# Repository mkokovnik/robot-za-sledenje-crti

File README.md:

# robot-za-sledenje-crti
mehatronski sistemi

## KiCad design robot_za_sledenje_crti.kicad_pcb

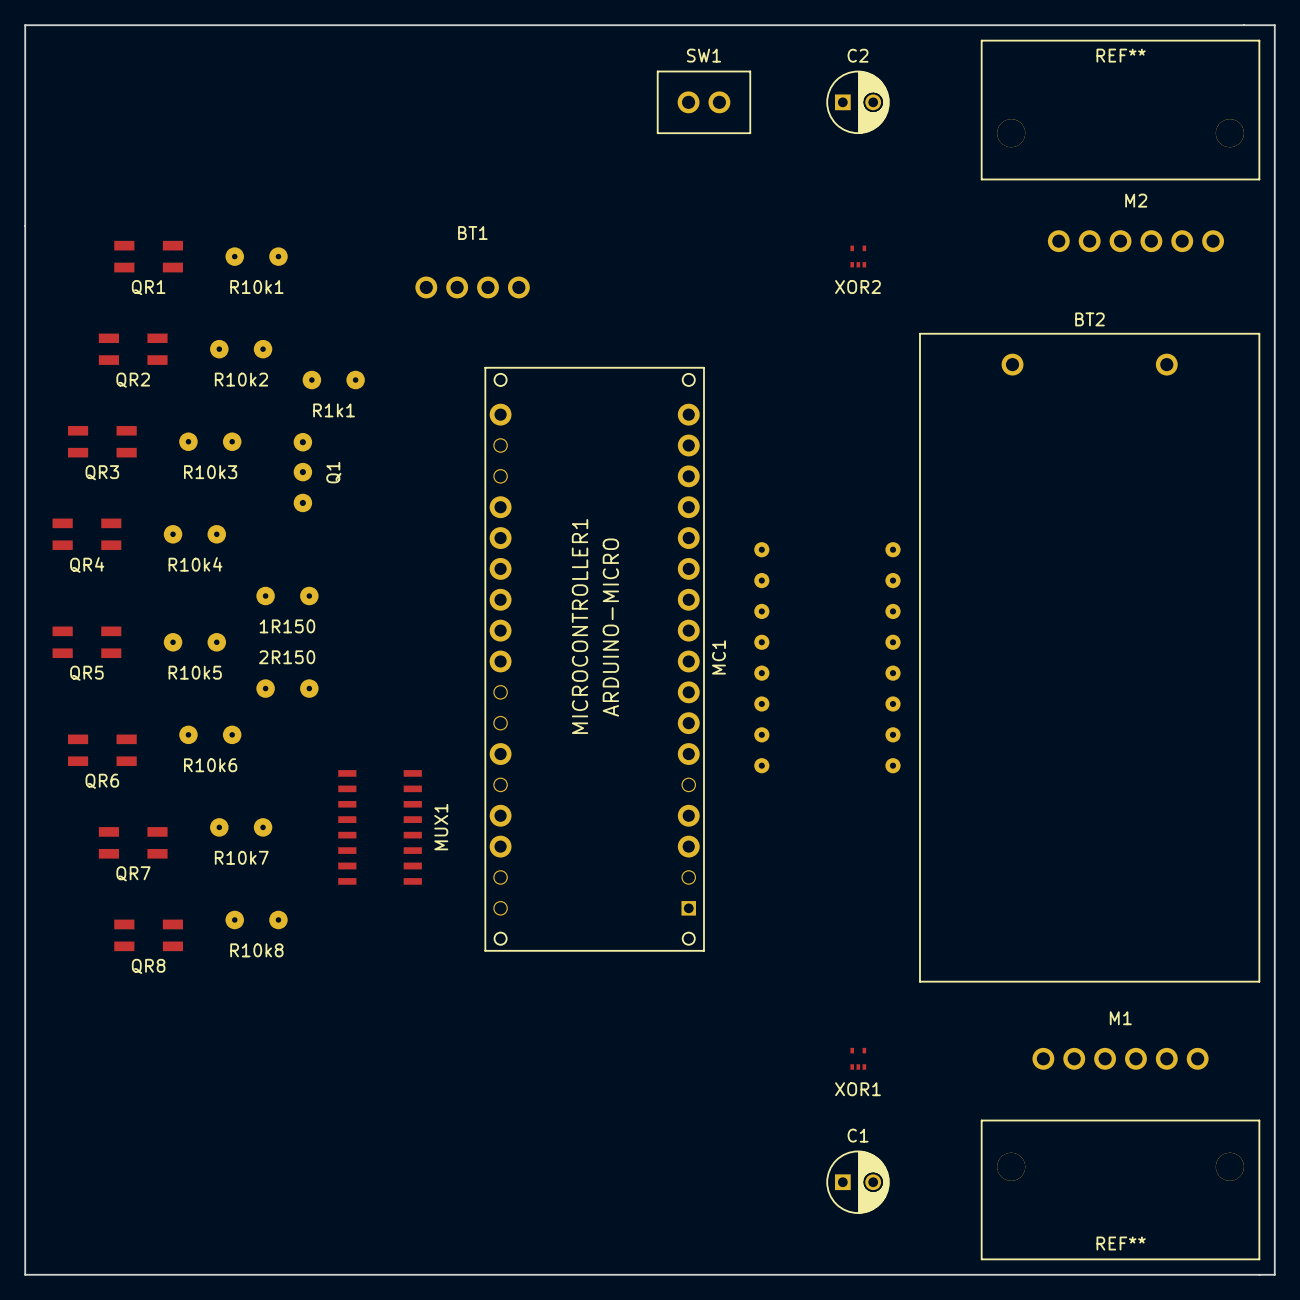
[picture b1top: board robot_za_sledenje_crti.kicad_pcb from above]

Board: 2 copper layers, 102.9 x 102.9 mm, 32 parts (0 on the bottom side), 37 nets, no tracks yet.

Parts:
1R150, 2R150: R; R150
BT1: JY-MCU; JY_MCU
BT2: Battery_Cell; Baterry
C1: CMD; C_Radial_D5_L6_P2.5
C2: CML; C_Radial_D5_L6_P2.5
M1, M2: Motor_Encoder; EM_Encoder
MC1: L293_MOTOR_CONTROLLER
MICROCONTROLLER1: ARDUINO-MICRO; ARDUINO_MICRO_SHIELD
MUX1: 4051; mux4051
Q1: Q_NPN_BCE; npn-10v
QR1, QR2, QR3, QR4, QR5, QR6, QR7, QR8: QRE1113
R1k1: R; R1k
R10k1, R10k2, R10k3, R10k4, R10k5, R10k6, R10k7, R10k8: R; R10k
SW1: SWITCH; switch
XOR1, XOR2: XOR-Gate; XOR-GATE

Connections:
+5V: BT1.4, M1.3, M2.3, MC1.1, MC1.9, MC1.16, R10k1.1, R10k2.1, R10k3.1, R10k4.1, R10k5.1, R10k6.1, R10k7.1, R10k8.1, XOR1.5, XOR2.5
ENCDA: M1.4, MICROCONTROLLER1.8, XOR1.1
ENCLA: M2.4, MICROCONTROLLER1.7, XOR2.1
GND: BT1.3, M1.6, M2.6, MC1.4, MC1.5, MC1.12, MC1.13, MUX1.6, MUX1.7, Q1.3, QR1.4, QR2.4, QR3.4, QR4.4, QR5.4, QR6.4, QR7.4, QR8.4, SW1.2, XOR1.3, XOR2.3
unnamed: 1R150.2, QR1.1
unnamed: 2R150.2, QR5.1
unnamed: BT1.1, MICROCONTROLLER1.3
unnamed: BT1.2, MICROCONTROLLER1.4
unnamed: BT2.2, SW1.1
unnamed: C1.1, M1.1, MC1.3
unnamed: C1.2, M1.2, MC1.6
unnamed: C2.1, M2.1, MC1.11
unnamed: C2.2, M2.2, MC1.14
unnamed: M1.5, XOR1.2
unnamed: M2.5, XOR2.2
unnamed: MUX1.1, QR5.3, R10k5.2
unnamed: MUX1.2, QR7.3, R10k7.2
unnamed: MUX1.4, QR8.3, R10k8.2
unnamed: MUX1.5, QR6.3, R10k6.2
unnamed: MUX1.12, QR4.3, R10k4.2
unnamed: MUX1.13, QR1.3, R10k1.2
unnamed: MUX1.14, QR2.3, R10k2.2
unnamed: MUX1.15, QR3.3, R10k3.2
unnamed: Q1.1, R1k1.1
unnamed: Q1.2, QR4.2, QR8.2
unnamed: QR1.2, QR2.1
unnamed: QR2.2, QR3.1
unnamed: QR3.2, QR4.1
unnamed: QR5.2, QR6.1
unnamed: QR6.2, QR7.1
unnamed: QR7.2, QR8.1
PWMD1: 1R150.1, 2R150.1, BT2.1, MC1.2, MC1.7, MC1.8
PWML1: MC1.10, MICROCONTROLLER1.10
PWML2: MC1.15, MICROCONTROLLER1.11
QR-ON: MICROCONTROLLER1.9, R1k1.2
S0: MICROCONTROLLER1.12, MUX1.11
S1: MICROCONTROLLER1.13, MUX1.10

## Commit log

2017-03-12 Revert "Add files via upload"
    This reverts commit 29cc3141b3bef5298213dbb906497494f2fa372c.
